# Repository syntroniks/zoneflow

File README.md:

# ZoneFlow

Open-source controller for 24 VAC sprinkler valves: 8 zones plus a master
valve or pump-start relay, a colour display with a knob, WiFi and Bluetooth
LE, and no cloud service.

> **Status: designed on paper. Not built. Not tested.**
> No ZoneFlow board has been made, no part has been printed and no firmware
> has run on a board. Every figure in this repository is a design value, a
> calculation or a simulation result. **Do not order boards yet**: the PCB
> layout is finished and has had an independent review, but nobody has gone
> through the review's pre-order checklist, no sample display panel has
> confirmed the flat cable, and the owner has not decided to order. ZoneFlow
> has no safety, EMC or radio certification.

Documentation and manual: <https://syntroniks.github.io/zoneflow/>

## What exists

| Part | State |
|---|---|
| Circuit design | Written with calculations and simulations; two independent reviews (A1, A2) and the answers to the firmware's questions, findings resolved ([hardware design](docs/design/hardware-design.md)) |
| Schematic | KiCad 10, 20 pages, generated from `hardware/netlist.yaml`, ERC clean ([PDF](hardware/zoneflow-a/output/zoneflow-a-schematic.pdf)) |
| Bill of materials | LCSC number, stock and price on every line but the coin cell, checked 2026-11-10 and 2026-11-11 ([cost estimate](docs/hardware/cost.md)) |
| PCB layout | Revision A, 114 x 110 mm, four layers, routed, DRC clean; [independently reviewed](docs/design/hardware-layout-review.md); fabrication files in `hardware/zoneflow-a/output/`. Not ordered: the [pre-order review](docs/hardware/review/index.md) by a person is open ([#11](https://github.com/syntroniks/zoneflow/issues/11)) |
| Enclosure | Parametric OpenSCAD model, 8 printed parts, STL and 3MF exports, and a printable test-fit kit generated from the board file; not printed |
| Standalone firmware | ESP-IDF; web interface, REST API, MQTT, OTA, display menus; host-tested and run in a soak simulation, never run on a board |
| ESPHome package | Compiles for the board; host-tested, never run on a board |
| Browser demo | The standalone firmware compiled to WebAssembly on simulated hardware: <https://syntroniks.github.io/zoneflow/try-it/>. A simulation, not a test of hardware |
| Release tooling | Web installer, release workflow, `zfflash`; no release yet |

## Features, as designed

- 8 zone outputs and 1 master-valve or pump-start output, 24 VAC, 0.5 A each continuous; a 4-zone build of the same board
- Powered from one Class 2 sprinkler transformer; input designed to survive 32 VAC
- Valve current measured: open valve, shorted valve, current with every valve off and loss of 24 VAC reported in plain words
- Hardware fail-safe: two keep-alive detectors and a relay in the valve common turn the valves off within about a second if the firmware stops
- Rain sensor, flow meter (with leak alarm) and spare inputs; current-limited 5 V supply for powered meters
- 2.0 inch colour display, rotary encoder and two buttons, one light per output
- Real-time clock with a CR2032 cell: schedules run without a network
- Two firmware options: standalone (ESP-IDF) or ESPHome
- 3D-printable indoor wall-mount enclosure with a separate wiring compartment

## Repository layout

| Path | Contents |
|---|---|
| `docs/` | Documentation site source (MkDocs): the user manual, and design documents in `docs/design/` |
| `docs/design/system-spec.md` | System specification, the source of truth |
| `hardware/` | KiCad project, netlist, pin map, BOM, simulations |
| `firmware/zoneflow-fw/` | Standalone firmware (ESP-IDF) and its web interface |
| `firmware/esphome/` | ESPHome package and its external components |
| `enclosure/` | Parametric enclosure source and print files |
| `tools/` | Build, release and documentation scripts |
| `mkdocs.yml`, `pyproject.toml`, `uv.lock` | Site configuration and pinned docs dependencies |

## Follow and contribute

- Progress log: [issue #1](https://github.com/syntroniks/zoneflow/issues/1)
- Status and roadmap: <https://syntroniks.github.io/zoneflow/status/>
- How to contribute: [docs/contributing.md](docs/contributing.md). Reviews of the circuit, the layout and the firmware help most now.

## Licences

Hardware and enclosure: CERN-OHL-P-2.0 (`hardware/LICENSE`,
`enclosure/LICENSE`). Documentation: CC-BY-4.0 (`docs/LICENSE`). Firmware,
tools and everything else: Apache-2.0 (`LICENSE` at the root). Material from
other projects keeps its own licence:
[third-party material](docs/third-party.md).

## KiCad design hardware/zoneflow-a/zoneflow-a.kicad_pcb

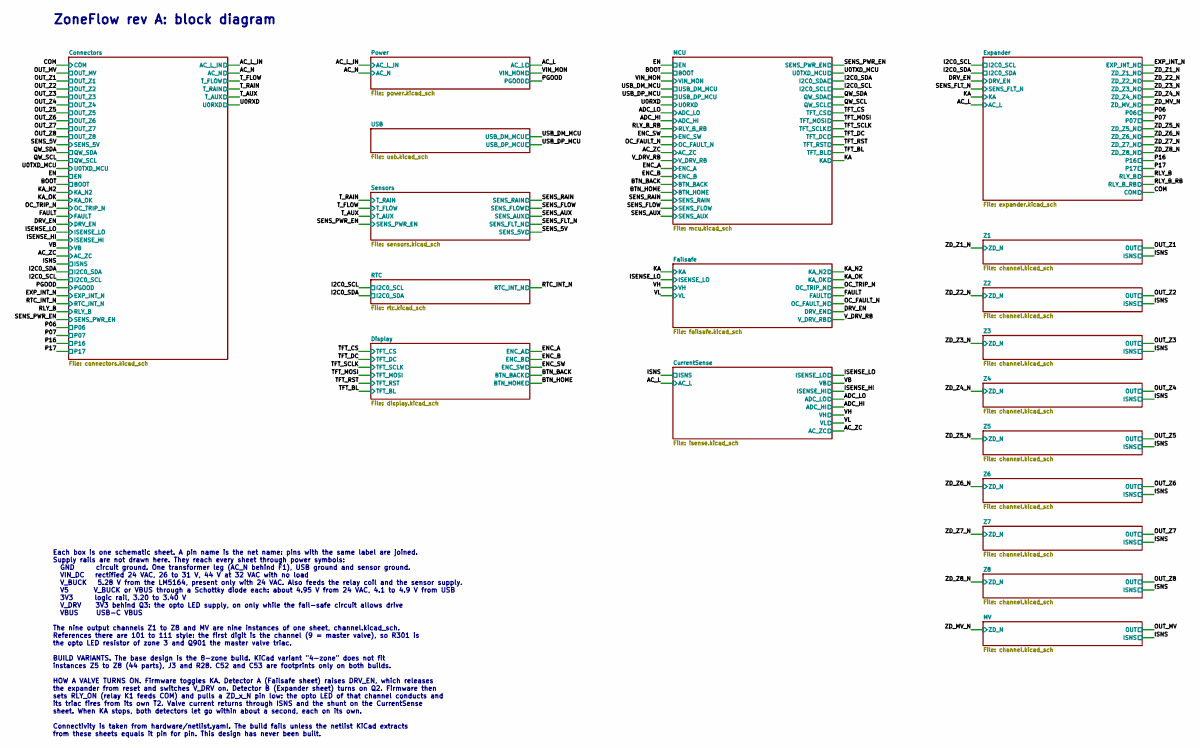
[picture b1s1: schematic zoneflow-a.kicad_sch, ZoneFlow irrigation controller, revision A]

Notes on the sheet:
ZoneFlow rev A: block diagram
Each box is one schematic sheet. A pin name is the net name: pins with the same label are joined. Supply rails are not drawn here. They reach every sheet through power symbols: GND circuit ground. One transformer leg (AC_N behind F1), USB ground and sensor ground. VIN_DC rectified 24 VAC, 26 to 31 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

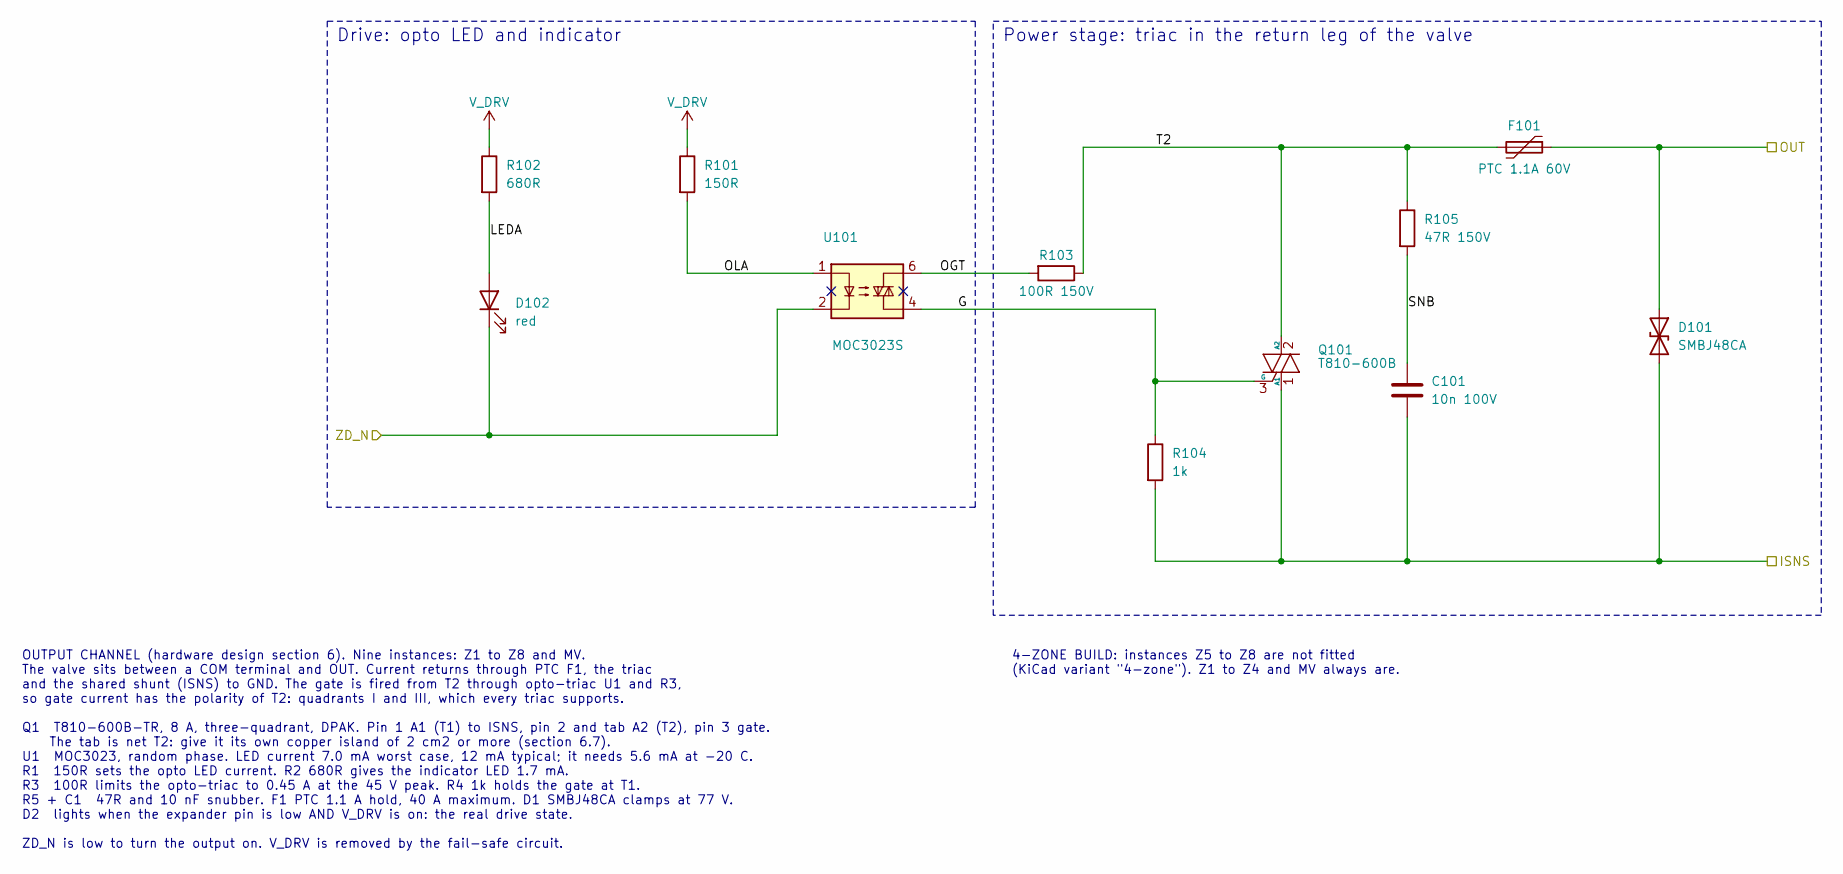
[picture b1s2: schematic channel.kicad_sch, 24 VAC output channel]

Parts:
C101: 10n 100V; C_0805_2012Metric; MPN CL21B103KCANNNC; LCSC C18741
D101: SMBJ48CA; D_SMB; MPN SMBJ48CA; LCSC C19077591
D102: red; LED_0603_1608Metric; MPN KT-0603R; LCSC C2286
F101: PTC 1.1A 60V; Fuse_2920_7451Metric; MPN BSMD2920-100-60V; LCSC C3020148
Q101: T810-600B; TO-252-2; MPN T810-600B-TR; LCSC C155588
R101: 150R; R_0603_1608Metric; MPN 0603WAF1500T5E; LCSC C22808
R102: 680R; R_0603_1608Metric; MPN 0603WAF6800T5E; LCSC C23228
R103: 100R 150V; R_0805_2012Metric; MPN 0805W8F1000T5E; LCSC C17408
R104: 1k; R_0603_1608Metric; MPN 0603WAF1001T5E; LCSC C21190
R105: 47R 150V; R_0805_2012Metric; MPN 0805W8F470JT5E; LCSC C17714
U101: MOC3023S; SMDIP-6_onsemi_646BY; MPN MOC3023SR2M; LCSC C40701

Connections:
/ISNS: C101.2, D101.2 (A2), Q101.1 (A1), R104.2; also elsewhere on the board
/OUT_Z1: D101.1 (A1), F101.1; also elsewhere on the board
/Z1/G: Q101.3 (G), R104.1, U101.4
/Z1/LEDA: D102.2 (A), R102.2
/Z1/OGT: R103.2, U101.6
/Z1/OLA: R101.2, U101.1
/Z1/SNB: C101.1, R105.2
/Z1/T2: F101.2, Q101.2 (A2), R103.1, R105.1
/ZD_Z1_N: D102.1 (K), U101.2; also elsewhere on the board
V_DRV: R101.1, R102.1; also elsewhere on the board

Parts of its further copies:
C201, C301, C401, C501, C601, C701, C801, C901: 10n 100V; C_0805_2012Metric; MPN CL21B103KCANNNC; LCSC C18741
D201, D301, D401, D501, D601, D701, D801, D901: SMBJ48CA; D_SMB; MPN SMBJ48CA; LCSC C19077591
D202, D302, D402, D502, D602, D702, D802, D902: red; LED_0603_1608Metric; MPN KT-0603R; LCSC C2286
F201, F301, F401, F501, F601, F701, F801, F901: PTC 1.1A 60V; Fuse_2920_7451Metric; MPN BSMD2920-100-60V; LCSC C3020148
Q201, Q301, Q401, Q501, Q601, Q701, Q801, Q901: T810-600B; TO-252-2; MPN T810-600B-TR; LCSC C155588
R201, R301, R401, R501, R601, R701, R801, R901: 150R; R_0603_1608Metric; MPN 0603WAF1500T5E; LCSC C22808
R202, R302, R402, R502, R602, R702, R802, R902: 680R; R_0603_1608Metric; MPN 0603WAF6800T5E; LCSC C23228
R203, R303, R403, R503, R603, R703, R803, R903: 100R 150V; R_0805_2012Metric; MPN 0805W8F1000T5E; LCSC C17408
R204, R304, R404, R504, R604, R704, R804, R904: 1k; R_0603_1608Metric; MPN 0603WAF1001T5E; LCSC C21190
R205, R305, R405, R505, R605, R705, R805, R905: 47R 150V; R_0805_2012Metric; MPN 0805W8F470JT5E; LCSC C17714
U201, U301, U401, U501, U601, U701, U801, U901: MOC3023S; SMDIP-6_onsemi_646BY; MPN MOC3023SR2M; LCSC C40701

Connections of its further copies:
/ISNS: C201.2, C301.2, C401.2, C501.2, C601.2, C701.2, C801.2, C901.2, D201.2 (A2), D301.2 (A2), D401.2 (A2), D501.2 (A2), D601.2 (A2), D701.2 (A2), D801.2 (A2), D901.2 (A2), Q201.1 (A1), Q301.1 (A1), Q401.1 (A1), Q501.1 (A1), Q601.1 (A1), Q701.1 (A1), Q801.1 (A1), Q901.1 (A1), R204.2, R304.2, R404.2, R504.2, R604.2, R704.2, R804.2, R904.2; also elsewhere on the board
/MV/G: Q901.3 (G), R904.1, U901.4
/MV/LEDA: D902.2 (A), R902.2
/MV/OGT: R903.2, U901.6
/MV/OLA: R901.2, U901.1
/MV/SNB: C901.1, R905.2
/MV/T2: F901.2, Q901.2 (A2), R903.1, R905.1
/OUT_MV: D901.1 (A1), F901.1; also elsewhere on the board
/OUT_Z2: D201.1 (A1), F201.1; also elsewhere on the board
/OUT_Z3: D301.1 (A1), F301.1; also elsewhere on the board
/OUT_Z4: D401.1 (A1), F401.1; also elsewhere on the board
/OUT_Z5: D501.1 (A1), F501.1; also elsewhere on the board
/OUT_Z6: D601.1 (A1), F601.1; also elsewhere on the board
/OUT_Z7: D701.1 (A1), F701.1; also elsewhere on the board
/OUT_Z8: D801.1 (A1), F801.1; also elsewhere on the board
/Z2/G: Q201.3 (G), R204.1, U201.4
/Z2/LEDA: D202.2 (A), R202.2
/Z2/OGT: R203.2, U201.6
/Z2/OLA: R201.2, U201.1
/Z2/SNB: C201.1, R205.2
/Z2/T2: F201.2, Q201.2 (A2), R203.1, R205.1
/Z3/G: Q301.3 (G), R304.1, U301.4
/Z3/LEDA: D302.2 (A), R302.2
/Z3/OGT: R303.2, U301.6
/Z3/OLA: R301.2, U301.1
/Z3/SNB: C301.1, R305.2
/Z3/T2: F301.2, Q301.2 (A2), R303.1, R305.1
/Z4/G: Q401.3 (G), R404.1, U401.4
/Z4/LEDA: D402.2 (A), R402.2
/Z4/OGT: R403.2, U401.6
/Z4/OLA: R401.2, U401.1
/Z4/SNB: C401.1, R405.2
/Z4/T2: F401.2, Q401.2 (A2), R403.1, R405.1
/Z5/G: Q501.3 (G), R504.1, U501.4
/Z5/LEDA: D502.2 (A), R502.2
/Z5/OGT: R503.2, U501.6
/Z5/OLA: R501.2, U501.1
/Z5/SNB: C501.1, R505.2
/Z5/T2: F501.2, Q501.2 (A2), R503.1, R505.1
/Z6/G: Q601.3 (G), R604.1, U601.4
/Z6/LEDA: D602.2 (A), R602.2
/Z6/OGT: R603.2, U601.6
/Z6/OLA: R601.2, U601.1
/Z6/SNB: C601.1, R605.2
/Z6/T2: F601.2, Q601.2 (A2), R603.1, R605.1
/Z7/G: Q701.3 (G), R704.1, U701.4
/Z7/LEDA: D702.2 (A), R702.2
/Z7/OGT: R703.2, U701.6
/Z7/OLA: R701.2, U701.1
/Z7/SNB: C701.1, R705.2
/Z7/T2: F701.2, Q701.2 (A2), R703.1, R705.1
/Z8/G: Q801.3 (G), R804.1, U801.4
/Z8/LEDA: D802.2 (A), R802.2
/Z8/OGT: R803.2, U801.6
/Z8/OLA: R801.2, U801.1
/Z8/SNB: C801.1, R805.2
/Z8/T2: F801.2, Q801.2 (A2), R803.1, R805.1
/ZD_MV_N: D902.1 (K), U901.2; also elsewhere on the board
/ZD_Z2_N: D202.1 (K), U201.2; also elsewhere on the board
/ZD_Z3_N: D302.1 (K), U301.2; also elsewhere on the board
/ZD_Z4_N: D402.1 (K), U401.2; also elsewhere on the board
/ZD_Z5_N: D502.1 (K), U501.2; also elsewhere on the board
/ZD_Z6_N: D602.1 (K), U601.2; also elsewhere on the board
/ZD_Z7_N: D702.1 (K), U701.2; also elsewhere on the board
/ZD_Z8_N: D802.1 (K), U801.2; also elsewhere on the board
V_DRV: R201.1, R202.1, R301.1, R302.1, R401.1, R402.1, R501.1, R502.1, R601.1, R602.1, R701.1, R702.1, R801.1, R802.1, R901.1, R902.1; also elsewhere on the board

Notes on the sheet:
Drive: opto LED and indicator
4-ZONE BUILD: instances Z5 to Z8 are not fitted (KiCad variant "4-zone"). Z1 to Z4 and MV always are.
Power stage: triac in the return leg of the valve
OUTPUT CHANNEL (hardware design section 6). Nine instances: Z1 to Z8 and MV. The valve sits between a COM terminal and OUT. Current returns through PTC F1, the triac and the shared shunt (ISNS) to GND. The gate is fired from T2 through opto-triac U1 and R3, so gate current has the polarity of T2: q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

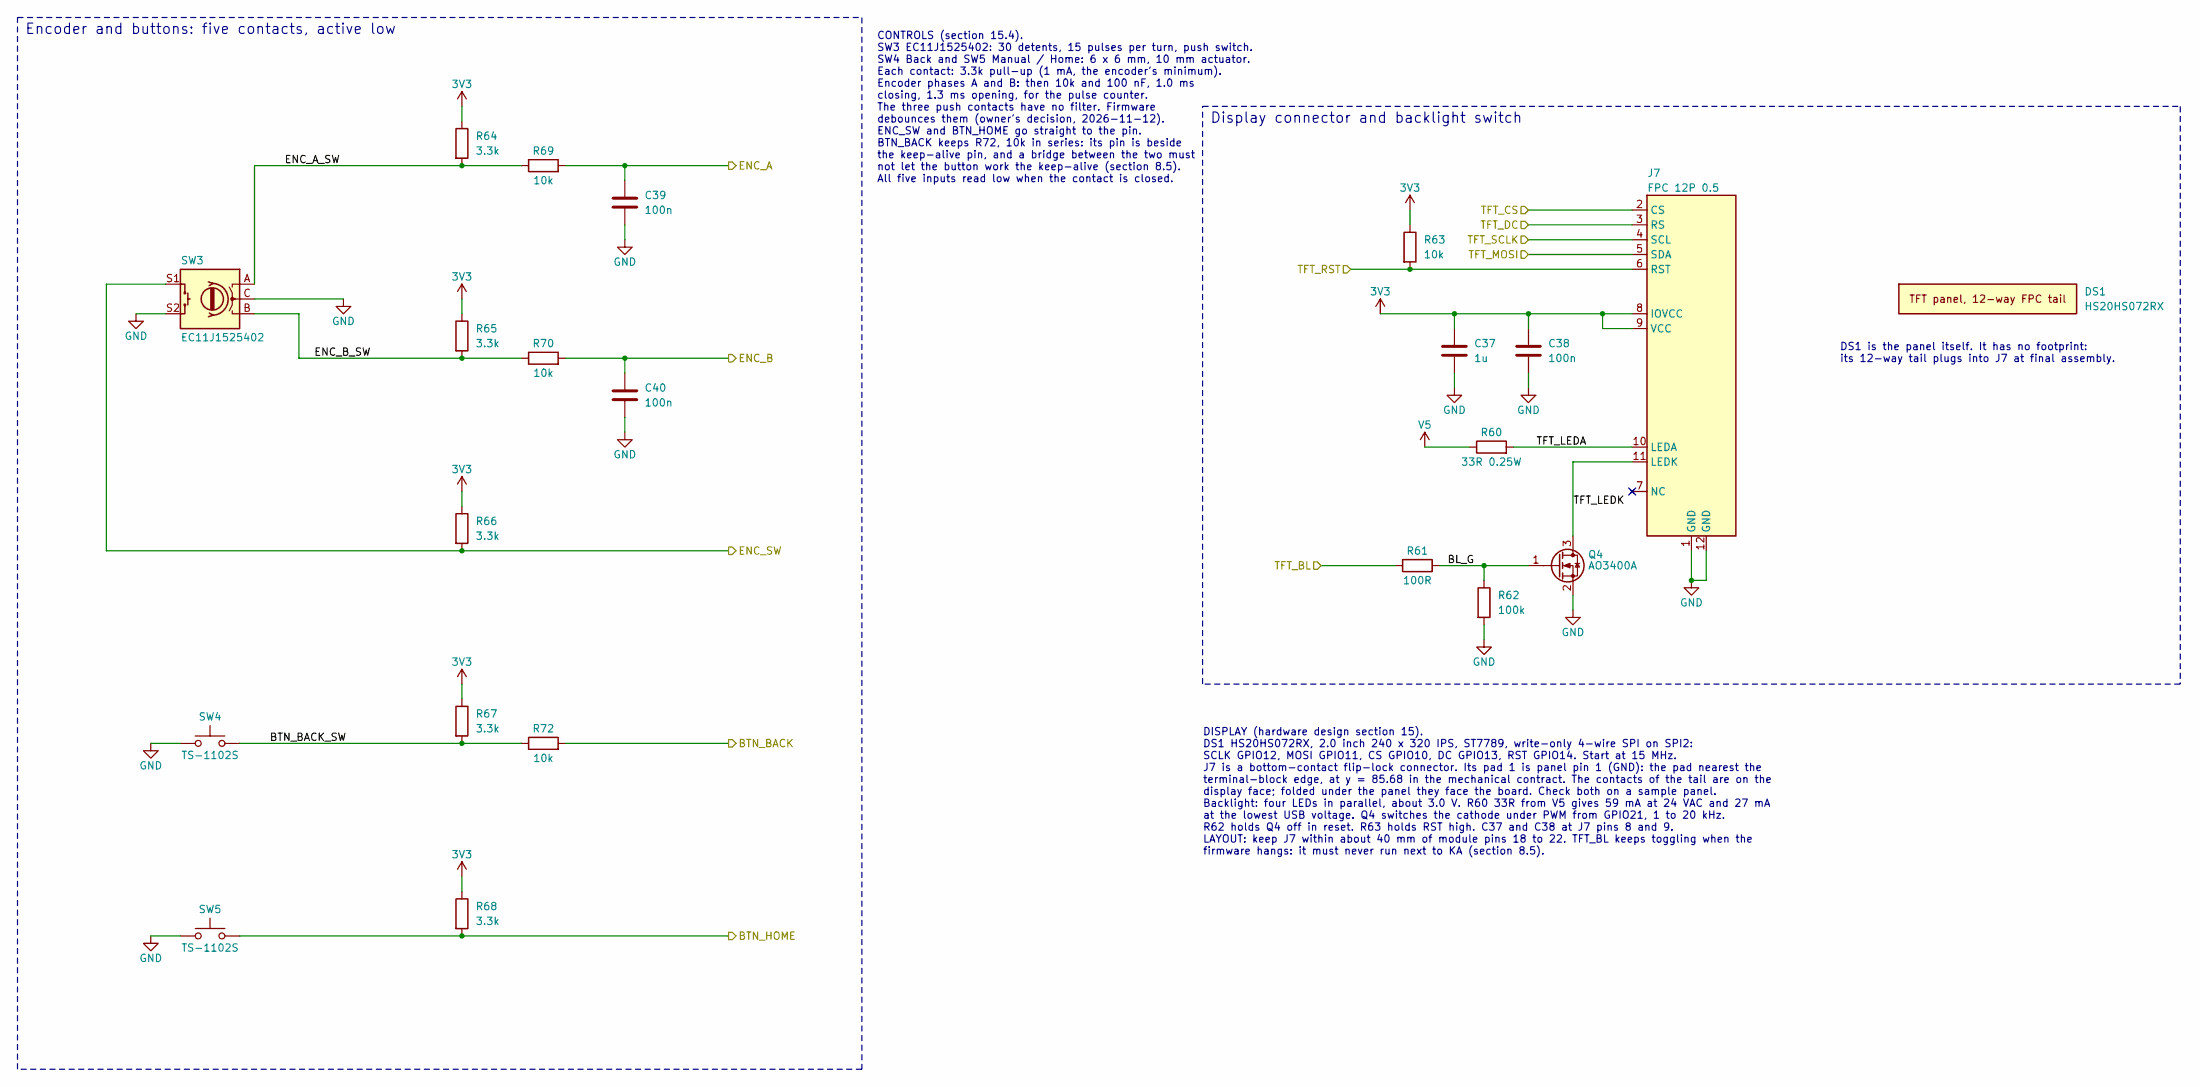
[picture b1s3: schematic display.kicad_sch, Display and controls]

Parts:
C37: 1u; C_0603_1608Metric; MPN CL10A105KB8NNNC; LCSC C15849
C38, C39, C40: 100n; C_0603_1608Metric; MPN CC0603KRX7R9BB104; LCSC C14663
DS1: HS20HS072RX; MPN HS20HS072RX; LCSC C5329582
J7: FPC 12P 0.5; FPC_XUNPU_FPC-05F-12PH20; MPN FPC-05F-12PH20; LCSC C2856799
Q4: AO3400A; SOT-23; MPN AO3400A; LCSC C20917
R60: 33R 0.25W; R_1206_3216Metric; MPN 1206W4F330JT5E; LCSC C18005
R61: 100R; R_0603_1608Metric; MPN 0603WAF1000T5E; LCSC C22775
R62: 100k; R_0603_1608Metric; MPN 0603WAF1003T5E; LCSC C25803
R63, R69, R70, R72: 10k; R_0603_1608Metric; MPN 0603WAF1002T5E; LCSC C25804
R64, R65, R66, R67, R68: 3.3k; R_0603_1608Metric; MPN 0603WAF3301T5E; LCSC C22978
SW3: EC11J1525402; RotaryEncoder_Alps_EC11J15; MPN EC11J1525402; LCSC C209762
SW4, SW5: TS-1102S; SW_Push_XKB_TS-1102S; MPN TS-1102S-C-M-B; LCSC C381050

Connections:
3V3: C37.1, C38.1, J7.8 (IOVCC), J7.9 (VCC), R63.1, R64.1, R65.1, R66.1, R67.1, R68.1; also elsewhere on the board
/BTN_BACK: R72.2; also elsewhere on the board
/BTN_HOME: R68.2, SW5.1; also elsewhere on the board
/Display/BL_G: Q4.1 (G), R61.2, R62.1
/Display/BTN_BACK_SW: R67.2, R72.1, SW4.1
/Display/ENC_A_SW: R64.2, R69.1, SW3.A
/Display/ENC_B_SW: R65.2, R70.1, SW3.B
/Display/TFT_LEDA: J7.10 (LEDA), R60.2
/Display/TFT_LEDK: J7.11 (LEDK), Q4.3 (D)
/ENC_A: C39.1, R69.2; also elsewhere on the board
/ENC_B: C40.1, R70.2; also elsewhere on the board
/ENC_SW: R66.2, SW3.S1; also elsewhere on the board
/TFT_BL: R61.1; also elsewhere on the board
/TFT_CS: J7.2 (CS); also elsewhere on the board
/TFT_DC: J7.3 (RS); also elsewhere on the board
/TFT_MOSI: J7.5 (SDA); also elsewhere on the board
/TFT_RST: J7.6 (RST), R63.2; also elsewhere on the board
/TFT_SCLK: J7.4 (SCL); also elsewhere on the board
GND: C37.2, C38.2, C39.2, C40.2, J7.1 (GND), J7.12 (GND), Q4.2 (S), R62.2, SW3.C, SW3.S2, SW4.2, SW5.2; also elsewhere on the board
V5: R60.1; also elsewhere on the board

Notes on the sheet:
Display connector and backlight switch
DISPLAY (hardware design section 15). DS1 HS20HS072RX, 2.0 inch 240 x 320 IPS, ST7789, write-only 4-wire SPI on SPI2: SCLK GPIO12, MOSI GPIO11, CS GPIO10, DC GPIO13, RST GPIO14. Start at 15 MHz. J7 is a bottom-contact flip-lock connector. Its pad 1 is panel pin 1 (GND): the pad nearest the terminal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
Encoder and buttons: five contacts, active low
CONTROLS (section 15.4). SW3 EC11J1525402: 30 detents, 15 pulses per turn, push switch. SW4 Back and SW5 Manual / Home: 6 x 6 mm, 10 mm actuator. Each contact: 3.3k pull-up (1 mA, the encoder's minimum). Encoder phases A and B: then 10k and 100 nF, 1.0 ms closing, 1.3 ms opening, for the pulse coun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
DS1 is the panel itself. It has no footprint: its 12-way tail plugs into J7 at final assembly.

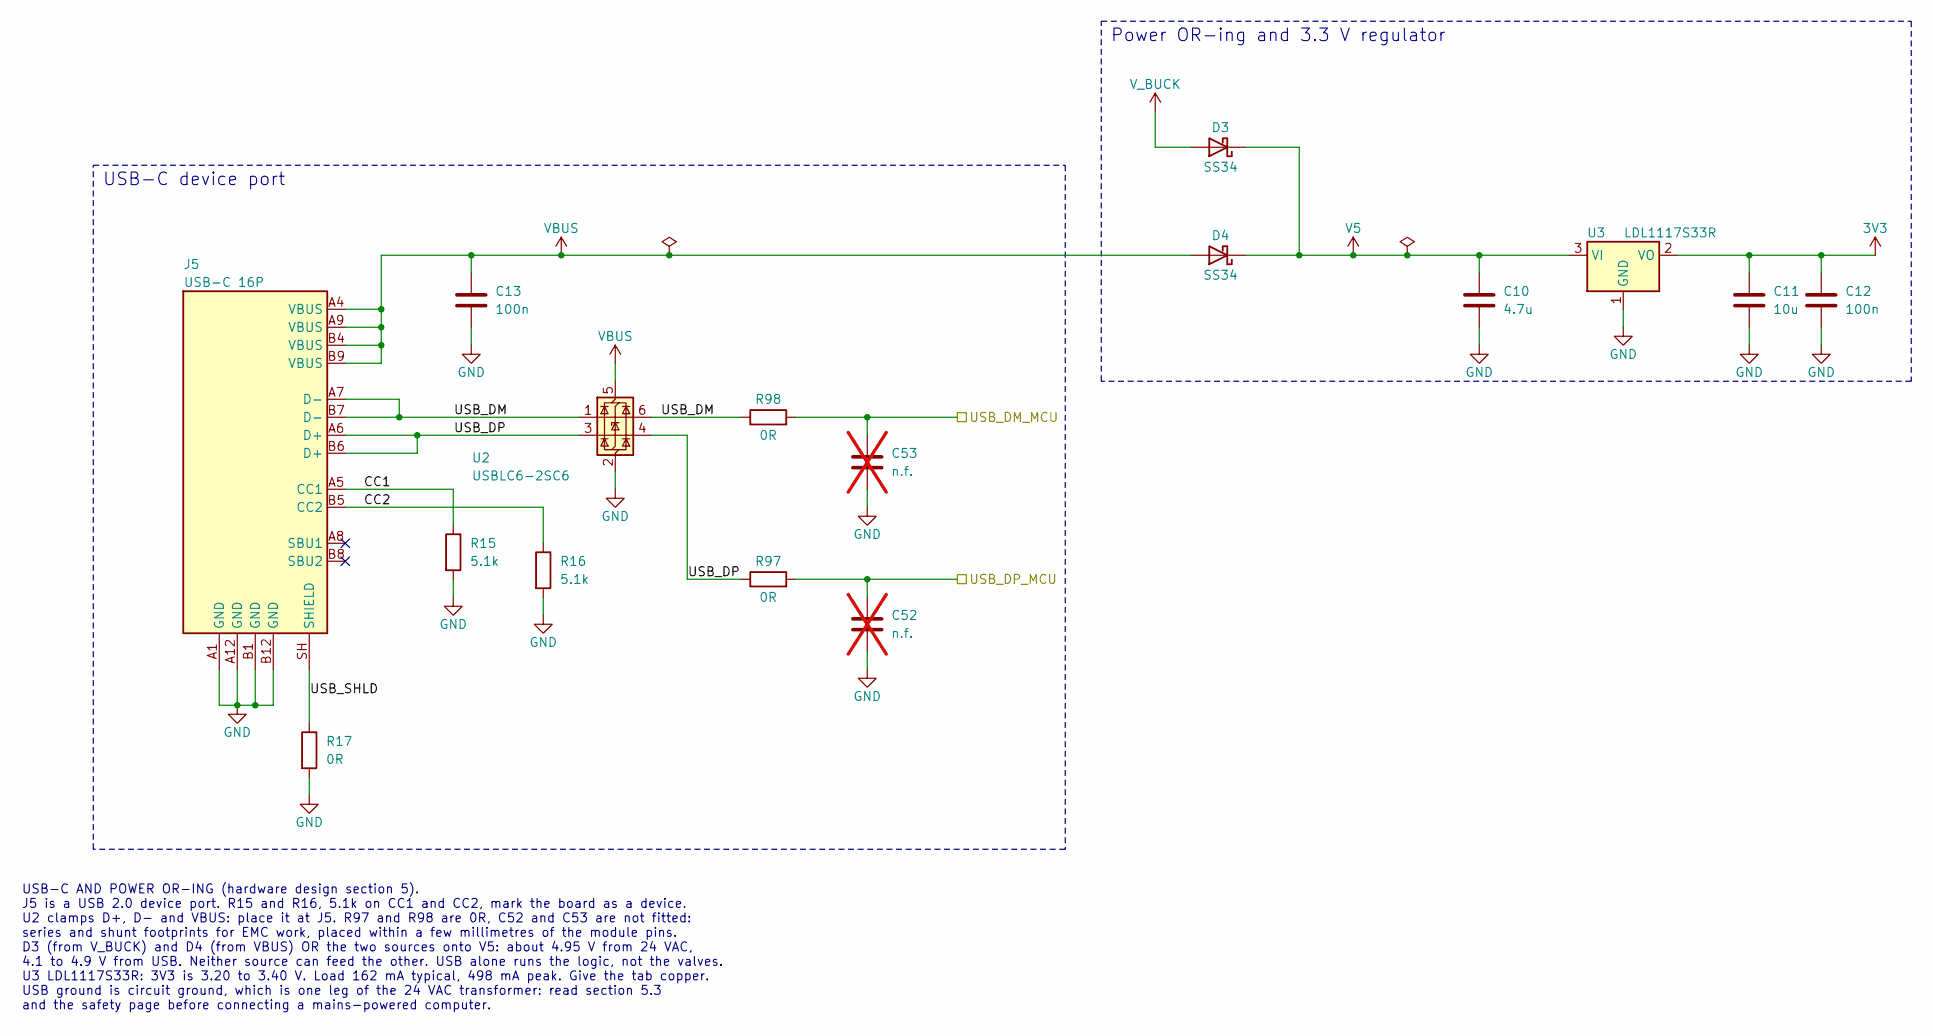
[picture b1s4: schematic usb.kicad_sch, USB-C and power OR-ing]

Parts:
C10: 4.7u; C_0805_2012Metric; MPN CL21A475KAQNNNE; LCSC C1779
C11: 10u; C_0805_2012Metric; MPN CL21A106KAYNNNE; LCSC C15850
C12, C13: 100n; C_0603_1608Metric; MPN CC0603KRX7R9BB104; LCSC C14663
C52, C53: n.f.; C_0603_1608Metric; not fitted
D3, D4: SS34; D_SMA; MPN SS34; LCSC C8678
J5: USB-C 16P; USB_C_Receptacle_HRO_TYPE-C-31-M-12; MPN TYPE-C-31-M-12; LCSC C165948
R15, R16: 5.1k; R_0603_1608Metric; MPN 0603WAF5101T5E; LCSC C23186
R17, R97, R98: 0R; R_0603_1608Metric; MPN 0603WAF0000T5E; LCSC C21189
U2: USBLC6-2SC6; SOT-23-6; MPN USBLC6-2SC6; LCSC C7519
U3: LDL1117S33R; SOT-223-3_TabPin2; MPN LDL1117S33R; LCSC C435835

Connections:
3V3: C11.1, C12.1, U3.2 (VO); also elsewhere on the board
/USB/CC1: J5.A5 (CC1), R15.1
/USB/CC2: J5.B5 (CC2), R16.1
/USB/USB_DM: J5.A7 (D-), J5.B7 (D-), R98.1, U2.1 (I/O1), U2.6 (I/O1)
/USB/USB_DP: J5.A6 (D+), J5.B6 (D+), R97.1, U2.3 (I/O2), U2.4 (I/O2)
/USB/USB_SHLD: J5.SH (SHIELD), R17.1
/USB_DM_MCU: C53.1, R98.2; also elsewhere on the board
/USB_DP_MCU: C52.1, R97.2; also elsewhere on the board
GND: C10.2, C11.2, C12.2, C13.2, C52.2, C53.2, J5.A1 (GND), J5.A12 (GND), J5.B1 (GND), J5.B12 (GND), R15.2, R16.2, R17.2, U2.2 (GND), U3.1 (GND); also elsewhere on the board
V5: C10.1, D3.1 (K), D4.1 (K), U3.3 (VI); also elsewhere on the board
VBUS: C13.1, D4.2 (A), J5.A4 (VBUS), J5.A9 (VBUS), J5.B4 (VBUS), J5.B9 (VBUS), U2.5 (VBUS)
V_BUCK: D3.2 (A); also elsewhere on the board

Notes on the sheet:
USB-C device port
Power OR-ing and 3.3 V regulator
USB-C AND POWER OR-ING (hardware design section 5). J5 is a USB 2.0 device port. R15 and R16, 5.1k on CC1 and CC2, mark the board as a device. U2 clamps D+, D- and VBUS: place it at J5. R97 and R98 are 0R, C52 and C53 are not fitted: series and shunt footprints for EMC work, placed within a few mil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

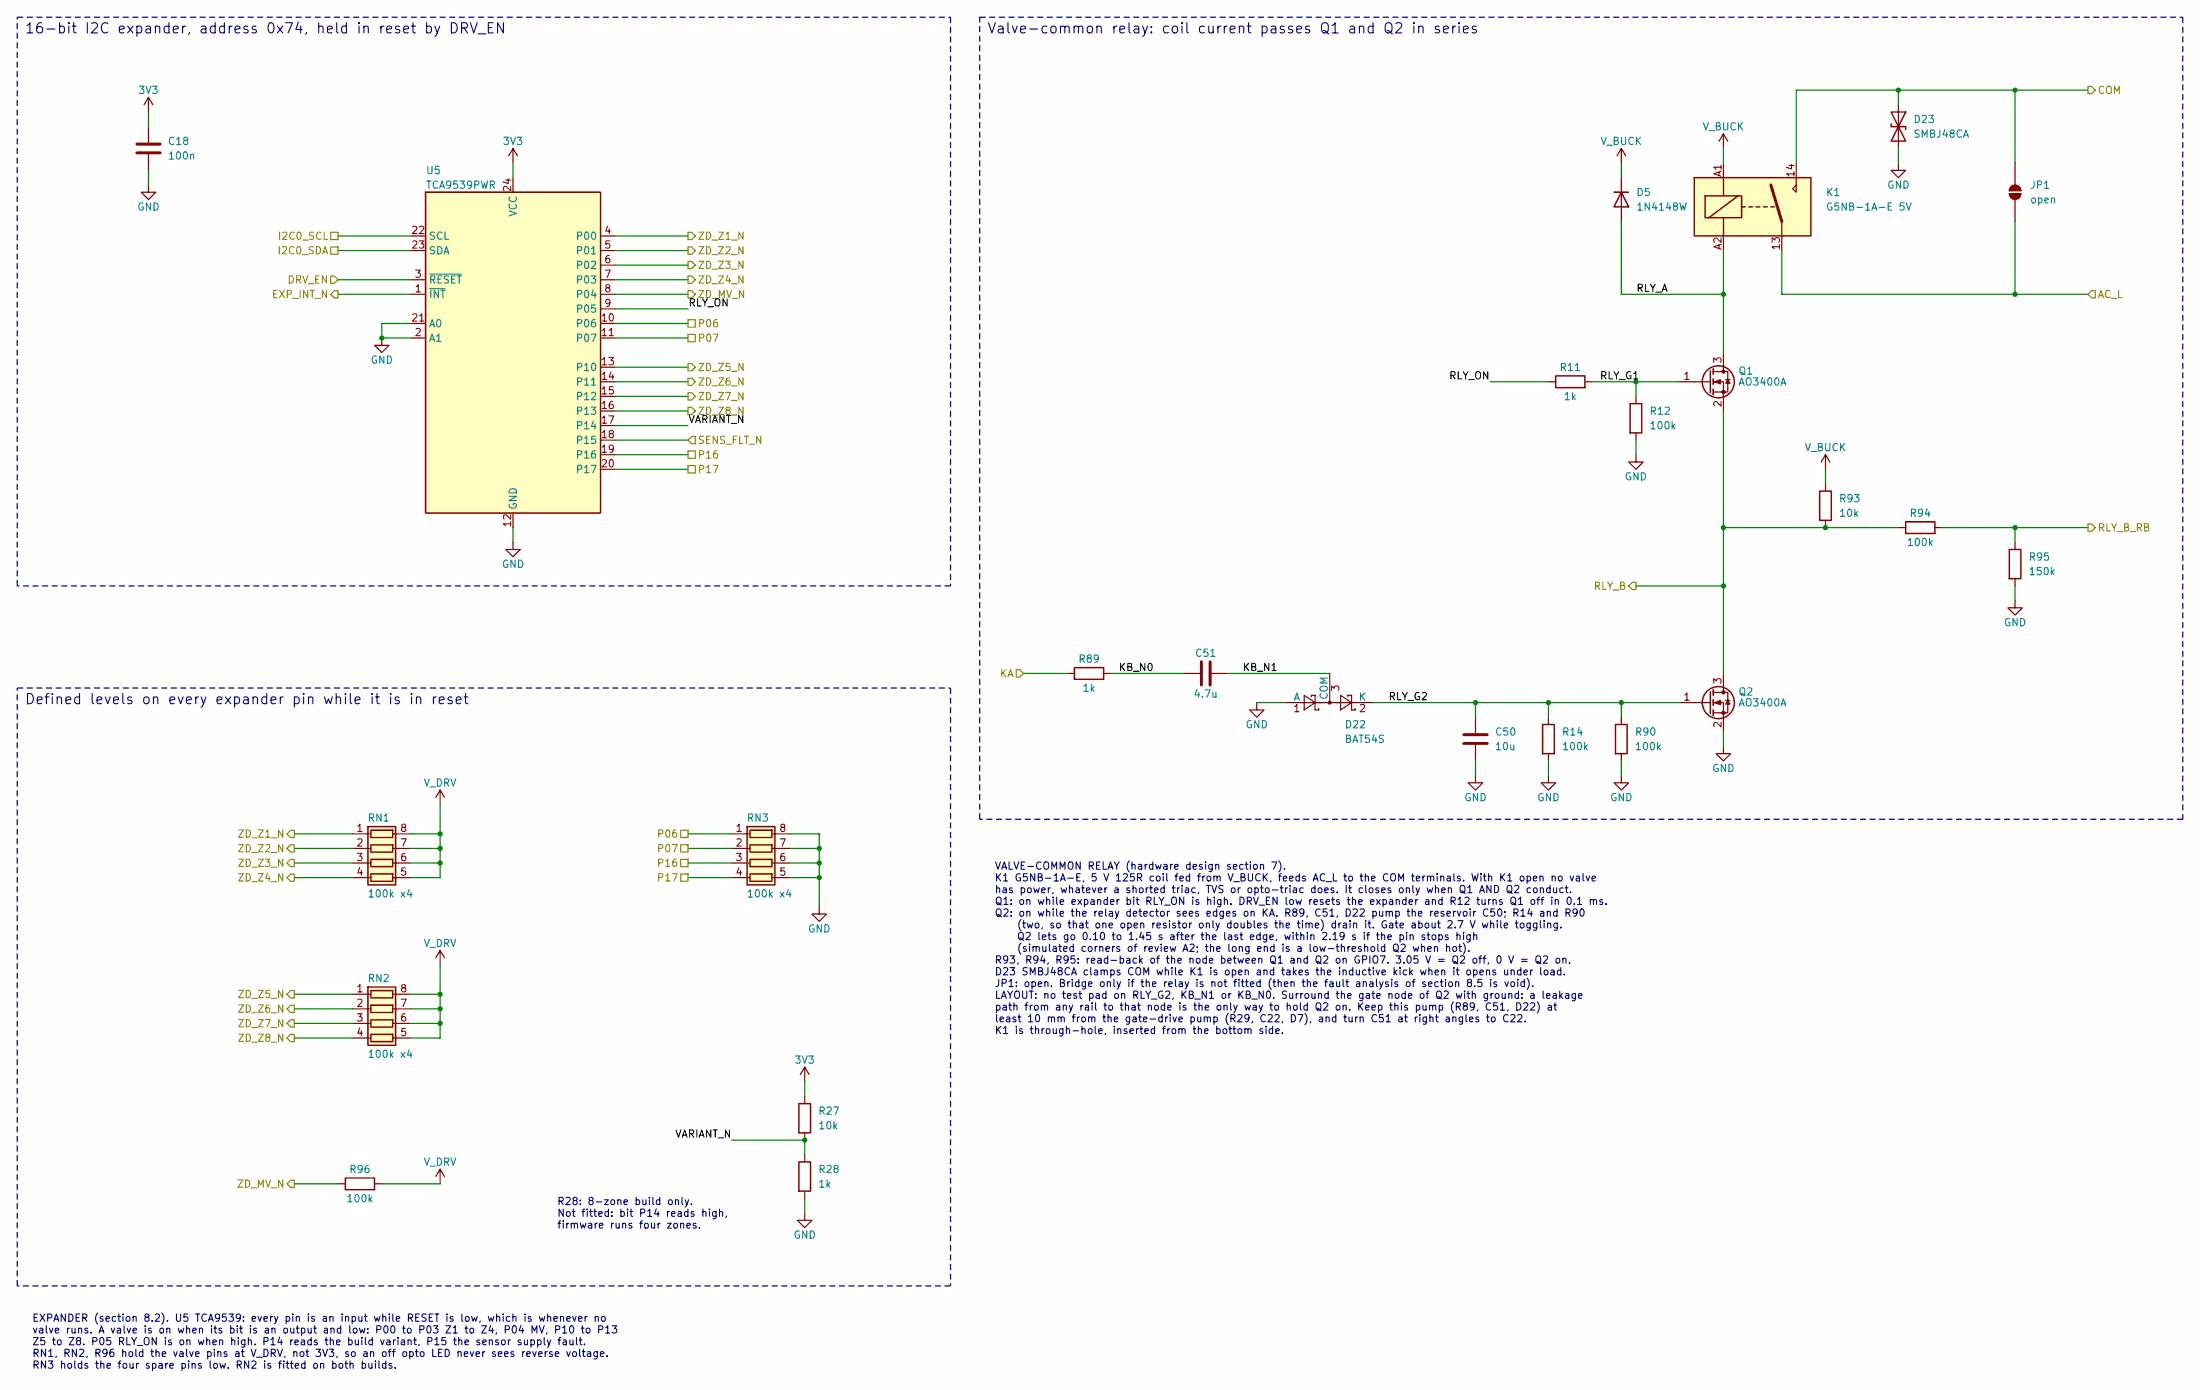
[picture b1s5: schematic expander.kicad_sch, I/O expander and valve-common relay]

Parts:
C18: 100n; C_0603_1608Metric; MPN CC0603KRX7R9BB104; LCSC C14663
C50: 10u; C_0805_2012Metric; MPN CL21A106KAYNNNE; LCSC C15850
C51: 4.7u; C_0805_2012Metric; MPN CL21A475KAQNNNE; LCSC C1779
D5: 1N4148W; D_SOD-123; MPN 1N4148W; LCSC C81598
D22: BAT54S; SOT-23; MPN BAT54S; LCSC C7420333
D23: SMBJ48CA; D_SMB; MPN SMBJ48CA; LCSC C19077591
JP1: open; SolderJumper-2_P1.3mm_Open_RoundedPad1.0x1.5mm
K1: G5NB-1A-E 5V; Relay_SPST_Omron_G5NB; MPN G5NB-1A-E-DC5V; LCSC C48746
Q1, Q2: AO3400A; SOT-23; MPN AO3400A; LCSC C20917
R11, R28, R89: 1k; R_0603_1608Metric; MPN 0603WAF1001T5E; LCSC C21190
R12, R14, R90, R94, R96: 100k; R_0603_1608Metric; MPN 0603WAF1003T5E; LCSC C25803
R27, R93: 10k; R_0603_1608Metric; MPN 0603WAF1002T5E; LCSC C25804
R95: 150k; R_0603_1608Metric; MPN 0603WAF1503T5E; LCSC C22807
RN1, RN2, RN3: 100k x4; R_Array_Convex_4x0603; MPN 4D03WGJ0104T5E; LCSC C1996
U5: TCA9539PWR; TSSOP-24_4.4x7.8mm_P0.65mm; MPN TCA9539PWR; LCSC C131972

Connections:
3V3: C18.1, R27.1, U5.24 (VCC); also elsewhere on the board
/AC_L: JP1.1 (A), K1.13; also elsewhere on the board
/COM: D23.1 (A1), JP1.2 (B), K1.14; also elsewhere on the board
/DRV_EN: U5.3 (~RESET); also elsewhere on the board
/EXP_INT_N: U5.1 (~INT); also elsewhere on the board
/Expander/KB_N0: C51.1, R89.2
/Expander/KB_N1: C51.2, D22.3 (COM)
/Expander/RLY_A: D5.2 (A), K1.A2, Q1.3 (D)
/Expander/RLY_G1: Q1.1 (G), R11.2, R12.1
/Expander/RLY_G2: C50.1, D22.2 (K), Q2.1 (G), R14.1, R90.1
/Expander/RLY_ON: R11.1, U5.9 (P05)
/Expander/VARIANT_N: R27.2, R28.1, U5.17 (P14)
/I2C0_SCL: U5.22 (SCL); also elsewhere on the board
/I2C0_SDA: U5.23 (SDA); also elsewhere on the board
/KA: R89.1; also elsewhere on the board
/P06: RN3.1 (R1.1), U5.10 (P06); also elsewhere on the board
/P07: RN3.2 (R2.1), U5.11 (P07); also elsewhere on the board
/P16: RN3.3 (R3.1), U5.19 (P16); also elsewhere on the board
/P17: RN3.4 (R4.1), U5.20 (P17); also elsewhere on the board
/RLY_B: Q1.2 (S), Q2.3 (D), R93.2, R94.1; also elsewhere on the board
/RLY_B_RB: R94.2, R95.1; also elsewhere on the board
/SENS_FLT_N: U5.18 (P15); also elsewhere on the board
/ZD_MV_N: R96.1, U5.8 (P04); also elsewhere on the board
/ZD_Z1_N: RN1.1 (R1.1), U5.4 (P00); also elsewhere on the board
/ZD_Z2_N: RN1.2 (R2.1), U5.5 (P01); also elsewhere on the board
/ZD_Z3_N: RN1.3 (R3.1), U5.6 (P02); also elsewhere on the board
/ZD_Z4_N: RN1.4 (R4.1), U5.7 (P03); also elsewhere on the board
/ZD_Z5_N: RN2.1 (R1.1), U5.13 (P10); also elsewhere on the board
/ZD_Z6_N: RN2.2 (R2.1), U5.14 (P11); also elsewhere on the board
/ZD_Z7_N: RN2.3 (R3.1), U5.15 (P12); also elsewhere on the board
/ZD_Z8_N: RN2.4 (R4.1), U5.16 (P13); also elsewhere on the board
GND: C18.2, C50.2, D22.1 (A), D23.2 (A2), Q2.2 (S), R12.2, R14.2, R28.2, R90.2, R95.2, RN3.5 (R4.2), RN3.6 (R3.2), RN3.7 (R2.2), RN3.8 (R1.2), U5.2 (A1), U5.12 (GND), U5.21 (A0); also elsewhere on the board
V_BUCK: D5.1 (K), K1.A1, R93.1; also elsewhere on the board
V_DRV: R96.2, RN1.5 (R4.2), RN1.6 (R3.2), RN1.7 (R2.2), RN1.8 (R1.2), RN2.5 (R4.2), RN2.6 (R3.2), RN2.7 (R2.2), RN2.8 (R1.2); also elsewhere on the board

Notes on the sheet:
VALVE-COMMON RELAY (hardware design section 7). K1 G5NB-1A-E, 5 V 125R coil fed from V_BUCK, feeds AC_L to the COM terminals. With K1 open no valve has power, whatever a shorted triac, TVS or opto-triac does. It closes only when Q1 AND Q2 conduct. Q1: on while expander bit RLY_ON is high. DRV_EN lo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
R28: 8-zone build only. Not fitted: bit P14 reads high, firmware runs four zones.
Valve-common relay: coil current passes Q1 and Q2 in series
16-bit I2C expander, address 0x74, held in reset by DRV_EN
EXPANDER (section 8.2). U5 TCA9539: every pin is an input while RESET is low, which is whenever no valve runs. A valve is on when its bit is an output and low: P00 to P03 Z1 to Z4, P04 MV, P10 to P13 Z5 to Z8. P05 RLY_ON is on when high. P14 reads the build variant, P15 the sensor supply fault. RN1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
Defined levels on every expander pin while it is in reset

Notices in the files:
firmware/zoneflow-fw/test/host/fake_board.hpp:
SPDX-License-Identifier: Apache-2.0
hardware/toolchain-test/ac_channel.kicad_sch:
ZoneFlow (open hardware, CERN-OHL-P-2.0)
hardware/zoneflow-a/zoneflow-a.kicad_pcb:
ZoneFlow rev A ENGINEERING PROTOTYPE CERN-OHL-P-2.0
